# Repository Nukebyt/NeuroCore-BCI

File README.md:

# NeuroDrive

NeuroCore is a battery-powered EEG + EMG acquisition board (ADS1299-4 + ADS131M04 + ESP32-S3 + IMU). It decodes biosignals into a small set of *intents* and sends them over the NeuroCore Intent Protocol (NIP) to device adapters: a toy RC truck first, then a BLE gamepad, smart plugs and a nano drone.

This is a hobby and research project. It is **not a medical device** and makes no medical claims.

- Progress: [docs/STATUS.md](docs/STATUS.md)
- Safety rules (read before touching hardware): [docs/safety.md](docs/safety.md)
- Design decisions: [docs/decisions/](docs/decisions/)

## Getting started (Fedora)

```bash
make venv        # Python 3.12 venv + dev tools + pre-commit hooks
make tools       # pinned verible for SystemVerilog lint
make check       # lint + format check
make test        # unit tests
make help        # all targets
```

Targets for parts that don't exist yet print `SKIP: ...` and succeed (see ADR-0001).

## Licence

Software and firmware: Apache-2.0. Hardware: CERN-OHL-W or CERN-OHL-P (to be decided before the Rev A release). Third-party attributions are in [NOTICE.md](NOTICE.md).

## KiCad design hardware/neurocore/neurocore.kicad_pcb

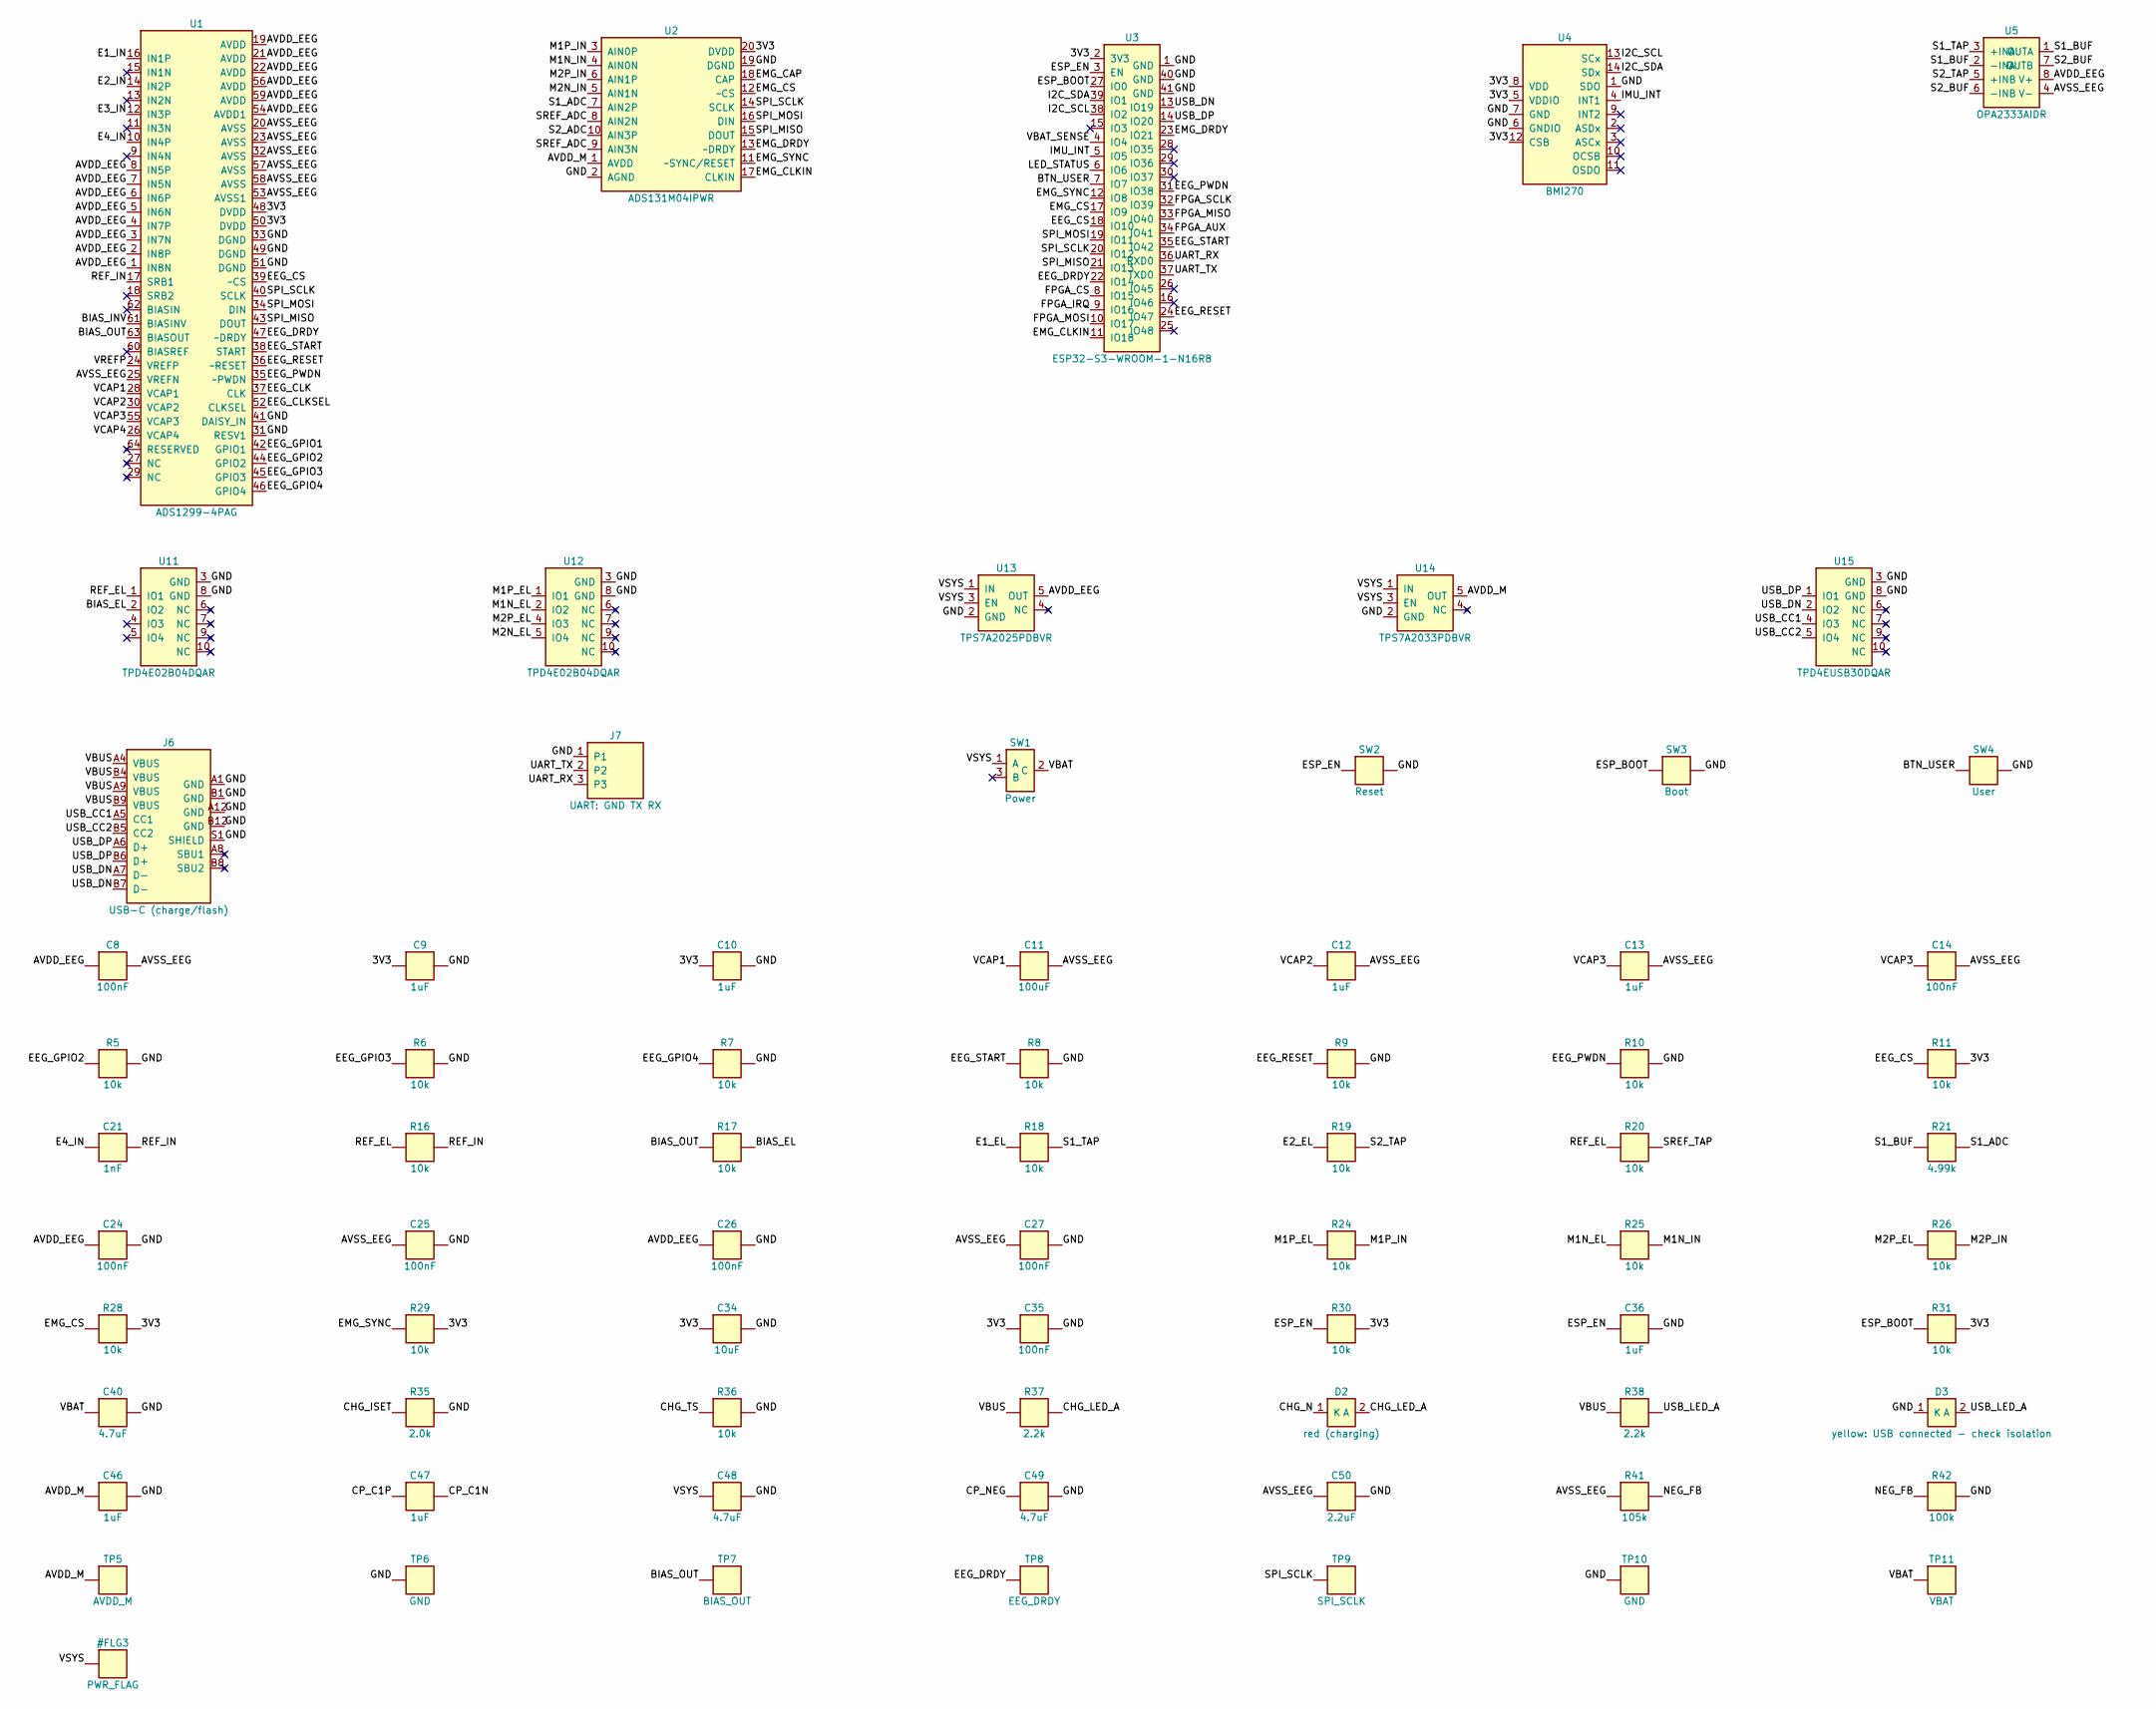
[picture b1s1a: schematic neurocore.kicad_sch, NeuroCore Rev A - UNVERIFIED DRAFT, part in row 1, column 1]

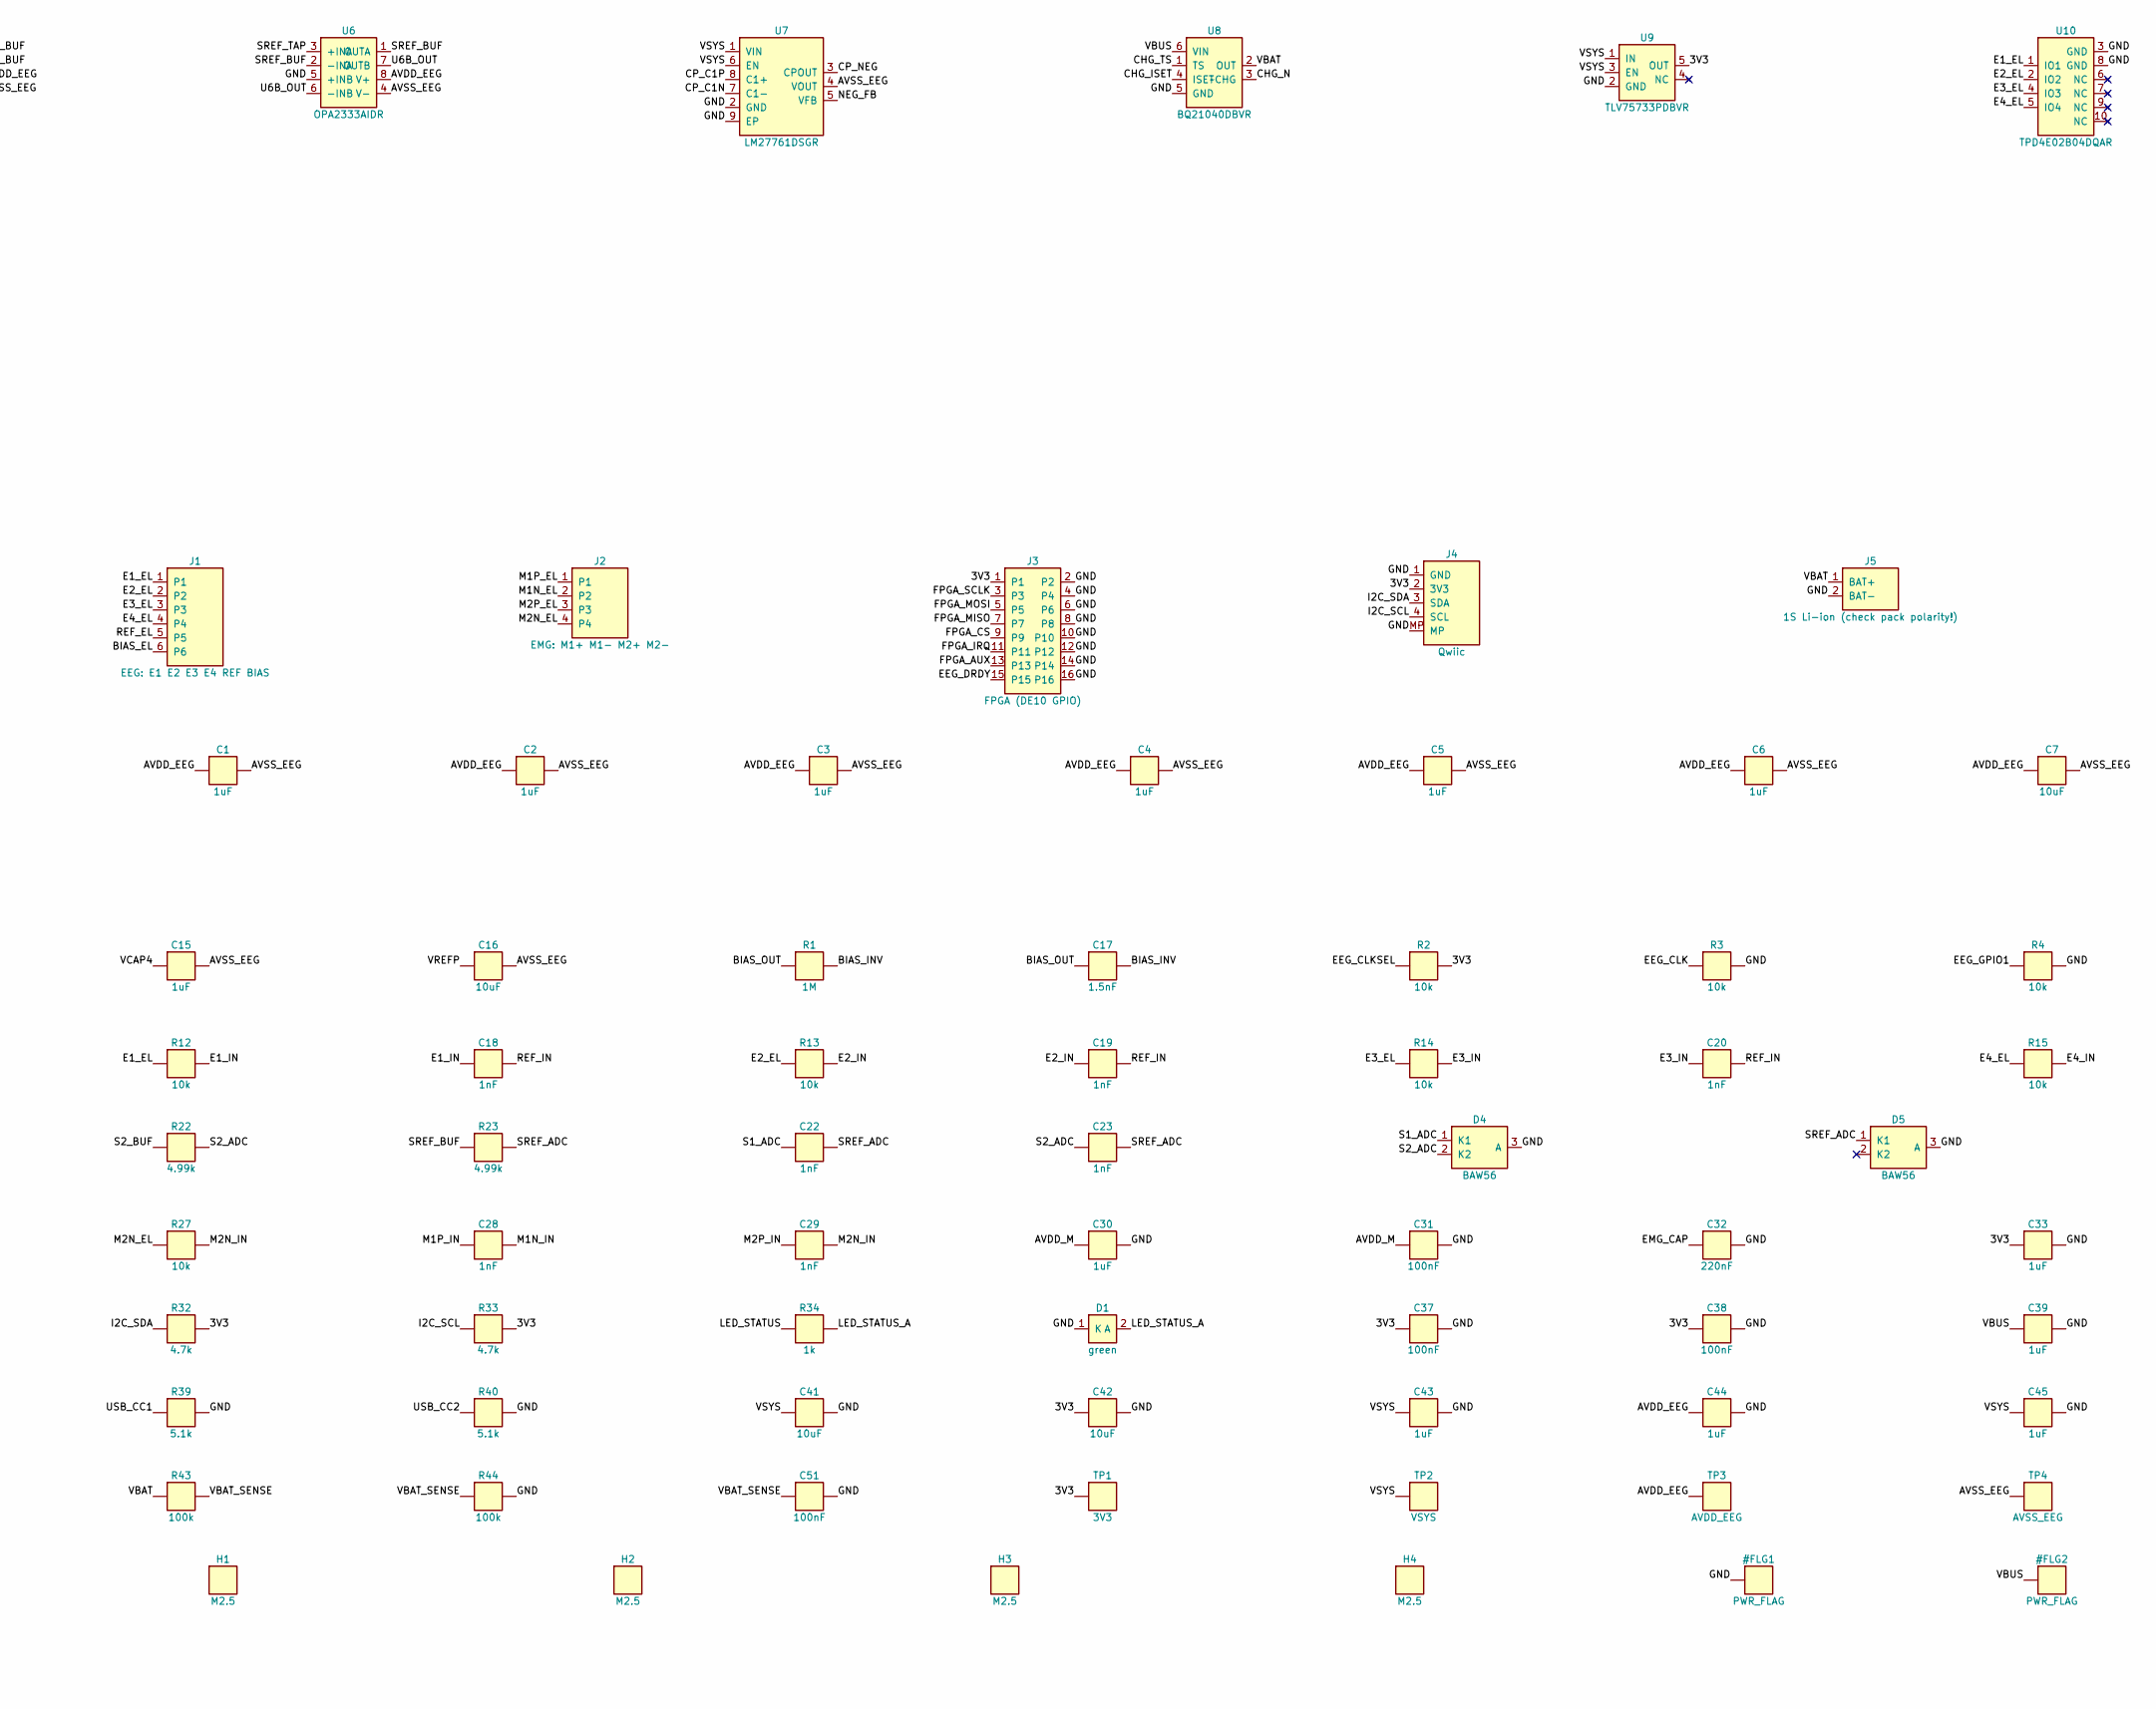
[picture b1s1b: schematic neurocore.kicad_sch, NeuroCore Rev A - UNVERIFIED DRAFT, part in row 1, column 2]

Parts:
C1, C2, C3, C4, C5, C6, C9, C10, C12, C13, C15, C30, C33, C36, C39, C43, C44, C45, C46, C47: 1uF; C_0603_1608Metric
C7, C16, C34, C41, C42: 10uF; C_0805_2012Metric
C8, C14, C24, C25, C26, C27, C31, C35, C37, C38, C51: 100nF; C_0603_1608Metric
C11: 100uF; C_1206_3216Metric
C17: 1.5nF; C_0603_1608Metric
C18, C19, C20, C21, C22, C23, C28, C29: 1nF; C_0603_1608Metric
C32: 220nF; C_0603_1608Metric
C40, C48, C49: 4.7uF; C_0805_2012Metric
C50: 2.2uF; C_0603_1608Metric
D1: green; LED_0603_1608Metric
D2: red (charging); LED_0603_1608Metric
D3: yellow: USB connected - check isolation; LED_0603_1608Metric
D4, D5: BAW56; SOT-23
H1, H2, H3, H4: M2.5; MountingHole_2.7mm_M2.5
J1: EEG: E1 E2 E3 E4 REF BIAS; PinHeader_1x06_P2.54mm_Vertical
J2: EMG: M1+ M1- M2+ M2-; PinHeader_1x04_P2.54mm_Vertical
J3: FPGA (DE10 GPIO); PinHeader_2x08_P2.54mm_Vertical
J4: Qwiic; JST_SH_SM04B-SRSS-TB_1x04-1MP_P1.00mm_Horizontal
J5: 1S Li-ion (check pack polarity!); JST_PH_B2B-PH-K_1x02_P2.00mm_Vertical
J6: USB-C (charge/flash); USB_C_Receptacle_HRO_TYPE-C-31-M-12
J7: UART: GND TX RX; PinHeader_1x03_P2.54mm_Vertical
R1: 1M; R_0603_1608Metric
R2, R3, R4, R5, R6, R7, R8, R9, R10, R11, R12, R13, R14, R15, R16, R17, R18, R19, R20, R24, R25, R26, R27, R28, R29, R30, R31, R36: 10k; R_0603_1608Metric
R21, R22, R23: 4.99k; R_0603_1608Metric
R32, R33: 4.7k; R_0603_1608Metric
R34: 1k; R_0603_1608Metric
R35: 2.0k; R_0603_1608Metric
R37, R38: 2.2k; R_0603_1608Metric
R39, R40: 5.1k; R_0603_1608Metric
R41: 105k; R_0603_1608Metric
R42, R43, R44: 100k; R_0603_1608Metric
SW1: Power; SW_SPDT_PCM12
SW2: Reset; SW_SPST_PTS810
SW3: Boot; SW_SPST_PTS810
SW4: User; SW_SPST_PTS810
TP1: 3V3; TestPoint_Pad_D1.0mm
TP2: VSYS; TestPoint_Pad_D1.0mm
TP3: AVDD_EEG; TestPoint_Pad_D1.0mm
TP4: AVSS_EEG; TestPoint_Pad_D1.0mm
TP5: AVDD_M; TestPoint_Pad_D1.0mm
TP6, TP10: GND; TestPoint_Pad_D1.0mm
TP7: BIAS_OUT; TestPoint_Pad_D1.0mm
TP8: EEG_DRDY; TestPoint_Pad_D1.0mm
TP9: SPI_SCLK; TestPoint_Pad_D1.0mm
TP11: VBAT; TestPoint_Pad_D1.0mm
U1: ADS1299-4PAG; TQFP-64_10x10mm_P0.5mm
U2: ADS131M04IPWR; TSSOP-20_4.4x6.5mm_P0.65mm
U3: ESP32-S3-WROOM-1-N16R8; ESP32-S3-WROOM-1
U4: BMI270; Bosch_LGA-14_3x2.5mm_P0.5mm
U5, U6: OPA2333AIDR; SOIC-8_3.9x4.9mm_P1.27mm
U7: LM27761DSGR; WSON-8-1EP_2x2mm_P0.5mm_EP0.9x1.6mm
U8: BQ21040DBVR; SOT-23-6
U9: TLV75733PDBVR; SOT-23-5
U10, U11, U12: TPD4E02B04DQAR; USON-10_2.5x1.0mm_P0.5mm
U13: TPS7A2025PDBVR; SOT-23-5
U14: TPS7A2033PDBVR; SOT-23-5
U15: TPD4EUSB30DQAR; USON-10_2.5x1.0mm_P0.5mm

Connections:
/3V3: C9.1, C10.1, C33.1, C34.1, C35.1, C37.1, C38.1, C42.1, J3.1, J4.2 (3V3), R2.2, R11.2, R28.2, R29.2, R30.2, R31.2, R32.2, R33.2, TP1.1, U1.48 (DVDD), U1.50 (DVDD), U2.20 (DVDD), U3.2 (3V3), U4.5 (VDDIO), U4.8 (VDD), U4.12 (CSB), U9.5 (OUT)
/AVDD_EEG: C1.1, C2.1, C3.1, C4.1, C5.1, C6.1, C7.1, C8.1, C24.1, C26.1, C44.1, TP3.1, U1.1 (IN8N), U1.2 (IN8P), U1.3 (IN7N), U1.4 (IN7P), U1.5 (IN6N), U1.6 (IN6P), U1.7 (IN5N), U1.8 (IN5P), U1.19 (AVDD), U1.21 (AVDD), U1.22 (AVDD), U1.54 (AVDD1), U1.56 (AVDD), U1.59 (AVDD), U5.8 (V+), U6.8 (V+), U13.5 (OUT)
/AVDD_M: C30.1, C31.1, C46.1, TP5.1, U2.1 (AVDD), U14.5 (OUT)
/AVSS_EEG: C1.2, C2.2, C3.2, C4.2, C5.2, C6.2, C7.2, C8.2, C11.2, C12.2, C13.2, C14.2, C15.2, C16.2, C25.1, C27.1, C50.1, R41.1, TP4.1, U1.20 (AVSS), U1.23 (AVSS), U1.25 (VREFN), U1.32 (AVSS), U1.53 (AVSS1), U1.57 (AVSS), U1.58 (AVSS), U5.4 (V-), U6.4 (V-), U7.4 (VOUT)
/BIAS_EL: J1.6, R17.2, U11.2 (IO2)
/BIAS_INV: C17.2, R1.2, U1.61 (BIASINV)
/BIAS_OUT: C17.1, R1.1, R17.1, TP7.1, U1.63 (BIASOUT)
/BTN_USER: SW4.1, U3.7 (IO7)
/CHG_ISET: R35.1, U8.4 (ISET)
/CHG_LED_A: D2.2 (A), R37.2
/CHG_N: D2.1 (K), U8.3 (~CHG)
/CHG_TS: R36.1, U8.1 (TS)
/CP_C1N: C47.2, U7.7 (C1-)
/CP_C1P: C47.1, U7.8 (C1+)
/CP_NEG: C49.1, U7.3 (CPOUT)
/E1_EL: J1.1, R12.1, R18.1, U10.1 (IO1)
/E1_IN: C18.1, R12.2, U1.16 (IN1P)
/E2_EL: J1.2, R13.1, R19.1, U10.2 (IO2)
/E2_IN: C19.1, R13.2, U1.14 (IN2P)
/E3_EL: J1.3, R14.1, U10.4 (IO3)
/E3_IN: C20.1, R14.2, U1.12 (IN3P)
/E4_EL: J1.4, R15.1, U10.5 (IO4)
/E4_IN: C21.1, R15.2, U1.10 (IN4P)
/EEG_CLK: R3.1, U1.37 (CLK)
/EEG_CLKSEL: R2.1, U1.52 (CLKSEL)
/EEG_CS: R11.1, U1.39 (~CS), U3.18 (IO10)
/EEG_DRDY: J3.15, TP8.1, U1.47 (~DRDY), U3.22 (IO14)
/EEG_GPIO1: R4.1, U1.42 (GPIO1)
/EEG_GPIO2: R5.1, U1.44 (GPIO2)
/EEG_GPIO3: R6.1, U1.45 (GPIO3)
/EEG_GPIO4: R7.1, U1.46 (GPIO4)
/EEG_PWDN: R10.1, U1.35 (~PWDN), U3.31 (IO38)
/EEG_RESET: R9.1, U1.36 (~RESET), U3.24 (IO47)
/EEG_START: R8.1, U1.38 (START), U3.35 (IO42)
/EMG_CAP: C32.1, U2.18 (CAP)
/EMG_CLKIN: U2.17 (CLKIN), U3.11 (IO18)
/EMG_CS: R28.1, U2.12 (~CS), U3.17 (IO9)
/EMG_DRDY: U2.13 (~DRDY), U3.23 (IO21)
/EMG_SYNC: R29.1, U2.11 (~SYNC/RESET), U3.12 (IO8)
/ESP_BOOT: R31.1, SW3.1, U3.27 (IO0)
/ESP_EN: C36.1, R30.1, SW2.1, U3.3 (EN)
/FPGA_AUX: J3.13, U3.34 (IO41)
/FPGA_CS: J3.9, U3.8 (IO15)
/FPGA_IRQ: J3.11, U3.9 (IO16)
/FPGA_MISO: J3.7, U3.33 (IO40)
/FPGA_MOSI: J3.5, U3.10 (IO17)
/FPGA_SCLK: J3.3, U3.32 (IO39)
/GND: C9.2, C10.2, C24.2, C25.2, C26.2, C27.2, C30.2, C31.2, C32.2, C33.2, C34.2, C35.2, C36.2, C37.2, C38.2, C39.2, C40.2, C41.2, C42.2, C43.2, C44.2, C45.2, C46.2, C48.2, C49.2, C50.2, C51.2, D1.1 (K), D3.1 (K), D4.3 (A), D5.3 (A), J3.2, J3.4, J3.6, J3.8, J3.10, J3.12, J3.14, J3.16, J4.1 (GND), J4.MP, J5.2 (BAT-), J6.A1 (GND), J6.A12 (GND), J6.B1 (GND), J6.B12 (GND), J6.S1 (SHIELD), J7.1, R3.2, R4.2, R5.2, R6.2, R7.2, R8.2, R9.2, R10.2, R35.2, R36.2, R39.2, R40.2, R42.2, R44.2, SW2.2, SW3.2, SW4.2, TP6.1, TP10.1, U1.31 (RESV1), U1.33 (DGND), U1.41 (DAISY_IN), U1.49 (DGND), U1.51 (DGND), U2.2 (AGND), U2.19 (DGND), U3.1 (GND), U3.40 (GND), U3.41 (GND), U4.1 (SDO), U4.6 (GNDIO), U4.7 (GND), U6.5 (+INB), U7.2 (GND), U7.9 (EP), U8.5 (GND), U9.2 (GND), U10.3 (GND), U10.8 (GND), U11.3 (GND), U11.8 (GND), U12.3 (GND), U12.8 (GND), U13.2 (GND), U14.2 (GND), U15.3 (GND), U15.8 (GND)
/I2C_SCL: J4.4 (SCL), R33.1, U3.38 (IO2), U4.13 (SCx)
/I2C_SDA: J4.3 (SDA), R32.1, U3.39 (IO1), U4.14 (SDx)
/IMU_INT: U3.5 (IO5), U4.4 (INT1)
/LED_STATUS: R34.1, U3.6 (IO6)
/LED_STATUS_A: D1.2 (A), R34.2
/M1N_EL: J2.2, R25.1, U12.2 (IO2)
/M1N_IN: C28.2, R25.2, U2.4 (AIN0N)
/M1P_EL: J2.1, R24.1, U12.1 (IO1)
/M1P_IN: C28.1, R24.2, U2.3 (AIN0P)
/M2N_EL: J2.4, R27.1, U12.5 (IO4)
/M2N_IN: C29.2, R27.2, U2.5 (AIN1N)
/M2P_EL: J2.3, R26.1, U12.4 (IO3)
/M2P_IN: C29.1, R26.2, U2.6 (AIN1P)
/NEG_FB: R41.2, R42.1, U7.5 (VFB)
/REF_EL: J1.5, R16.1, R20.1, U11.1 (IO1)
/REF_IN: C18.2, C19.2, C20.2, C21.2, R16.2, U1.17 (SRB1)
/S1_ADC: C22.1, D4.1 (K1), R21.2, U2.7 (AIN2P)
/S1_BUF: R21.1, U5.1 (OUTA), U5.2 (-INA)
/S1_TAP: R18.2, U5.3 (+INA)
/S2_ADC: C23.1, D4.2 (K2), R22.2, U2.10 (AIN3P)
/S2_BUF: R22.1, U5.6 (-INB), U5.7 (OUTB)
/S2_TAP: R19.2, U5.5 (+INB)
/SPI_MISO: U1.43 (DOUT), U2.15 (DOUT), U3.21 (IO13)
/SPI_MOSI: U1.34 (DIN), U2.16 (DIN), U3.19 (IO11)
/SPI_SCLK: TP9.1, U1.40 (SCLK), U2.14 (SCLK), U3.20 (IO12)
/SREF_ADC: C22.2, C23.2, D5.1 (K1), R23.2, U2.8 (AIN2N), U2.9 (AIN3N)
/SREF_BUF: R23.1, U6.1 (OUTA), U6.2 (-INA)
/SREF_TAP: R20.2, U6.3 (+INA)
/U6B_OUT: U6.6 (-INB), U6.7 (OUTB)
/UART_RX: J7.3, U3.36 (RXD0)
/UART_TX: J7.2, U3.37 (TXD0)
/USB_CC1: J6.A5 (CC1), R39.1, U15.4 (IO3)
/USB_CC2: J6.B5 (CC2), R40.1, U15.5 (IO4)
/USB_DN: J6.A7 (D-), J6.B7 (D-), U3.13 (IO19), U15.2 (IO2)
/USB_DP: J6.A6 (D+), J6.B6 (D+), U3.14 (IO20), U15.1 (IO1)
/USB_LED_A: D3.2 (A), R38.2
/VBAT: C40.1, J5.1 (BAT+), R43.1, SW1.2 (C), TP11.1, U8.2 (OUT)
/VBAT_SENSE: C51.1, R43.2, R44.1, U3.4 (IO4)
/VBUS: C39.1, J6.A4 (VBUS), J6.A9 (VBUS), J6.B4 (VBUS), J6.B9 (VBUS), R37.1, R38.1, U8.6 (VIN)
/VCAP1: C11.1, U1.28 (VCAP1)
/VCAP2: C12.1, U1.30 (VCAP2)
/VCAP3: C13.1, C14.1, U1.55 (VCAP3)
/VCAP4: C15.1, U1.26 (VCAP4)
/VREFP: C16.1, U1.24 (VREFP)
/VSYS: C41.1, C43.1, C45.1, C48.1, SW1.1 (A), TP2.1, U7.1 (VIN), U7.6 (EN), U9.1 (IN), U9.3 (EN), U13.1 (IN), U13.3 (EN), U14.1 (IN), U14.3 (EN)

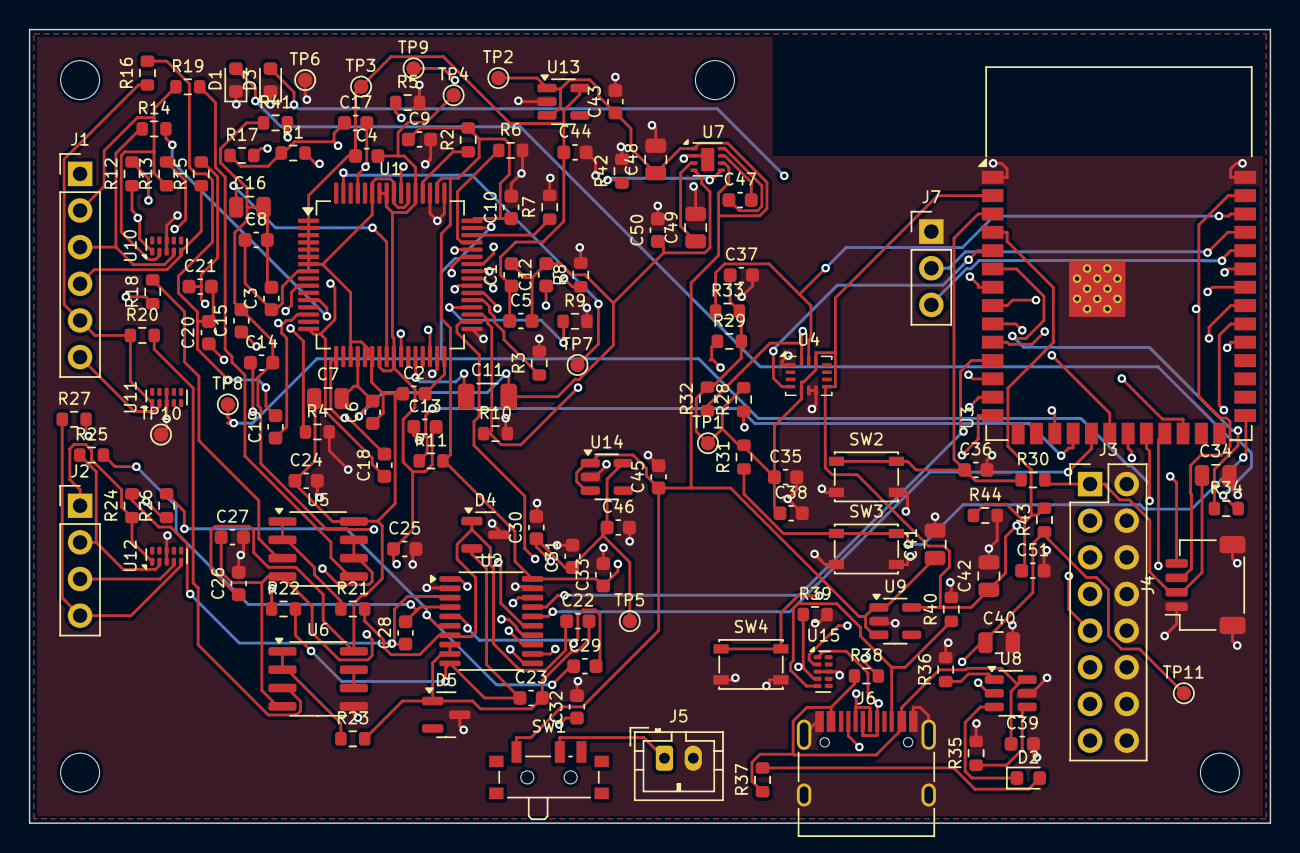
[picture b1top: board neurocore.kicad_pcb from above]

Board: 4 copper layers, 86.0 x 55.0 mm, 141 parts (0 on the bottom side), 93 nets.

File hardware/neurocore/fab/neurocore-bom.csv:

"Refs","Value","Footprint","Note","Qty"
"C1,C2,C3,C4,C5,C6,C9,C10,C12,C13,C15,C30,C33,C36,C39,C43,C44,C45,C46,C47","1uF","Capacitor_SMD:C_0603_1608Metric","ADS131M04 DVDD,AVDD 1 uF (Table 5-1),AVDD1-AVSS1 (pin 54),BQ21040 VIN 1-10 uF,DVDD pin 48,DVDD pin 50,EN RC,LM27761 C1 flying,TPS7A2025 IN (CIN 1 uF),TPS7A2025 OUT (COUT >= 1 uF),TPS7A2033 IN,TPS7A2033 OUT","20"
"C7,C16,C34,C41,C42","10uF","Capacitor_SMD:C_0805_2012Metric","TLV757 IN,TLV757 OUT,VREFP to VREFN(=AVSS), min 10 uF (p. 7),bulk, §11,module supply","5"
"C8,C14,C24,C25,C26,C27,C31,C35,C37,C38,C51","100nF","Capacitor_SMD:C_0603_1608Metric","BMI270 VDD (§7.2),BMI270 VDDIO (§7.2),OPA2333 V+,OPA2333 V-,§11","11"
"C11","100uF","Capacitor_SMD:C_1206_3216Metric","pin 28; C0G/tantalum if vibration (§11)","1"
"C17","1.5nF","Capacitor_SMD:C_0603_1608Metric","bias feedback, DS Fig. on p. 63","1"
"C18,C19,C20,C21,C22,C23,C28,C29","1nF","Capacitor_SMD:C_0603_1608Metric","C0G,C0G, differential (§12.1)","8"
"C32","220nF","Capacitor_SMD:C_0603_1608Metric","CAP 220 nF to DGND (Table 5-1)","1"
"C40,C48,C49","4.7uF","Capacitor_SMD:C_0805_2012Metric","BQ21040 OUT 1-10 uF,LM27761 C2 input,LM27761 C3 CPOUT","3"
"C50","2.2uF","Capacitor_SMD:C_0603_1608Metric","LM27761 C4 LDO out","1"
"D1","green","LED_SMD:LED_0603_1608Metric","status","1"
"D2","red (charging)","LED_SMD:LED_0603_1608Metric","","1"
"D3","yellow: USB connected - check isolation","LED_SMD:LED_0603_1608Metric","","1"
"D4,D5","BAW56","Package_TO_SOT_SMD:SOT-23","shadow-lane clamp,shadow-lane clamp (K2 unused)","2"
"J1","EEG: E1 E2 E3 E4 REF BIAS","Connector_PinHeader_2.54mm:PinHeader_1x06_P2.54mm_Vertical","","1"
"J2","EMG: M1+ M1- M2+ M2-","Connector_PinHeader_2.54mm:PinHeader_1x04_P2.54mm_Vertical","","1"
"J3","FPGA (DE10 GPIO)","Connector_PinHeader_2.54mm:PinHeader_2x08_P2.54mm_Vertical","","1"
"J4","Qwiic","Connector_JST:JST_SH_SM04B-SRSS-TB_1x04-1MP_P1.00mm_Horizontal","","1"
"J5","1S Li-ion (check pack polarity!)","Connector_JST:JST_PH_B2B-PH-K_1x02_P2.00mm_Vertical","","1"
"J6","USB-C (charge/flash)","Connector_USB:USB_C_Receptacle_HRO_TYPE-C-31-M-12","","1"
"J7","UART: GND TX RX","Connector_PinHeader_2.54mm:PinHeader_1x03_P2.54mm_Vertical","","1"
"R1","1M","Resistor_SMD:R_0603_1608Metric","bias feedback, DS Fig. on p. 63","1"
"R2,R3,R4,R5,R6,R7,R8,R9,R10,R11,R12,R13,R14,R15,R16,R17,R18,R19,R20,R24,R25,R26,R27,R28,R29,R30,R31,R36","10k","Resistor_SMD:R_0603_1608Metric","EN RC 10k/1uF (DS §9),bias electrode series resistor,don't float digital inputs (§10.1.1),electrode series resistor,electrode series resistor (safety rule 2),held low until MCU drives (power-up §11.1),internal osc; two-state pin via >=10k (p. 6 note 1),no NTC: TS to VSS via 10k (pin table),shadow tap series R,unused GPIO to DGND via >=10k (p. 6)","28"
"R21,R22,R23","4.99k","Resistor_SMD:R_0603_1608Metric","limits clamp current if a buffer rails","3"
"R32,R33","4.7k","Resistor_SMD:R_0603_1608Metric","","2"
"R34","1k","Resistor_SMD:R_0603_1608Metric","","1"
"R35","2.0k","Resistor_SMD:R_0603_1608Metric","I = 540 AΩ / 2.0k ≈ 270 mA (KISET, DS §7)","1"
"R37,R38","2.2k","Resistor_SMD:R_0603_1608Metric","","2"
"R39,R40","5.1k","Resistor_SMD:R_0603_1608Metric","USB-C sink Rd","2"
"R41","105k","Resistor_SMD:R_0603_1608Metric","R1: VOUT = -1.22(R1+R2)/R2 = -2.50 V","1"
"R42,R43,R44","100k","Resistor_SMD:R_0603_1608Metric","R2 >= 50k (DS 7.2.2.4)","3"
"SW1","Power","Button_Switch_SMD:SW_SPDT_PCM12","","1"
"SW2","Reset","Button_Switch_SMD:SW_SPST_PTS810","","1"
"SW3","Boot","Button_Switch_SMD:SW_SPST_PTS810","","1"
"SW4","User","Button_Switch_SMD:SW_SPST_PTS810","","1"
"U1","ADS1299-4PAG","Package_QFP:TQFP-64_10x10mm_P0.5mm","EEG ADC, bipolar ±2.5 V","1"
"U2","ADS131M04IPWR","Package_SO:TSSOP-20_4.4x6.5mm_P0.65mm","EMG + shadow-EEG ADC","1"
"U3","ESP32-S3-WROOM-1-N16R8","RF_Module:ESP32-S3-WROOM-1","MCU","1"
"U4","BMI270","Package_LGA:Bosch_LGA-14_3x2.5mm_P0.5mm","IMU (I2C)","1"
"U5,U6","OPA2333AIDR","Package_SO:SOIC-8_3.9x4.9mm_P1.27mm","shadow-lane REF buffer + spare,shadow-lane buffers (DNP-able)","2"
"U7","LM27761DSGR","Package_SON:WSON-8-1EP_2x2mm_P0.5mm_EP0.9x1.6mm","-2.5 V analog rail","1"
"U8","BQ21040DBVR","Package_TO_SOT_SMD:SOT-23-6","1S Li-ion charger, ~270 mA","1"
"U9","TLV75733PDBVR","Package_TO_SOT_SMD:SOT-23-5","3.3 V digital, 1 A","1"
"U10,U11,U12","TPD4E02B04DQAR","Package_SON:USON-10_2.5x1.0mm_P0.5mm","EEG electrode ESD (bidirectional),EMG electrode ESD,REF/BIAS ESD","3"
"U13","TPS7A2025PDBVR","Package_TO_SOT_SMD:SOT-23-5","+2.5 V analog (ADS1299), 7 uVrms","1"
"U14","TPS7A2033PDBVR","Package_TO_SOT_SMD:SOT-23-5","+3.3 V analog (ADS131M04)","1"
"U15","TPD4EUSB30DQAR","Package_SON:USON-10_2.5x1.0mm_P0.5mm","USB ESD","1"
